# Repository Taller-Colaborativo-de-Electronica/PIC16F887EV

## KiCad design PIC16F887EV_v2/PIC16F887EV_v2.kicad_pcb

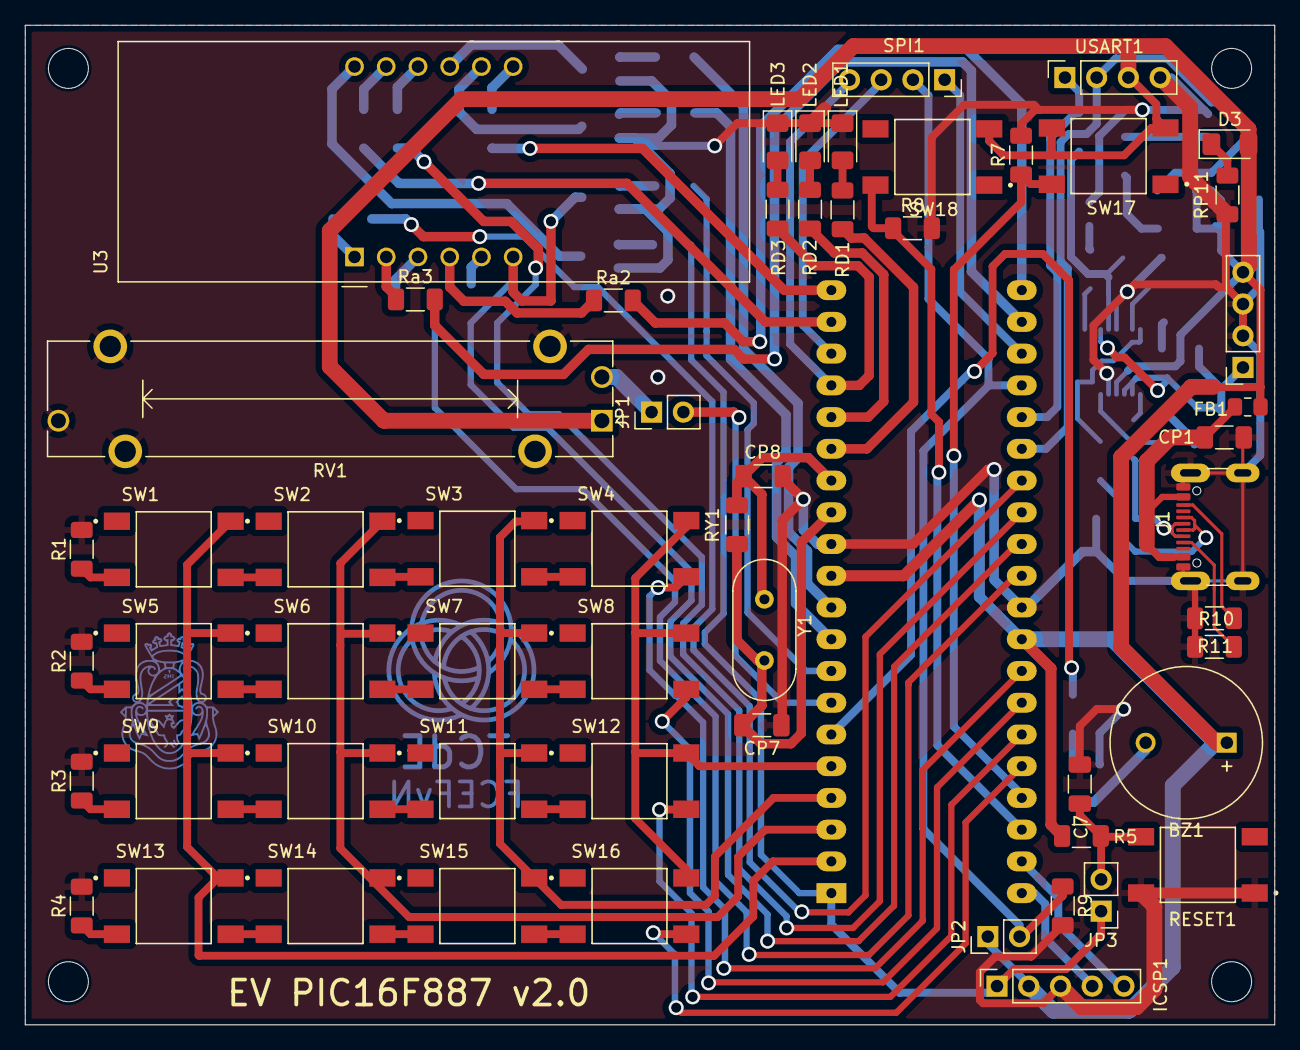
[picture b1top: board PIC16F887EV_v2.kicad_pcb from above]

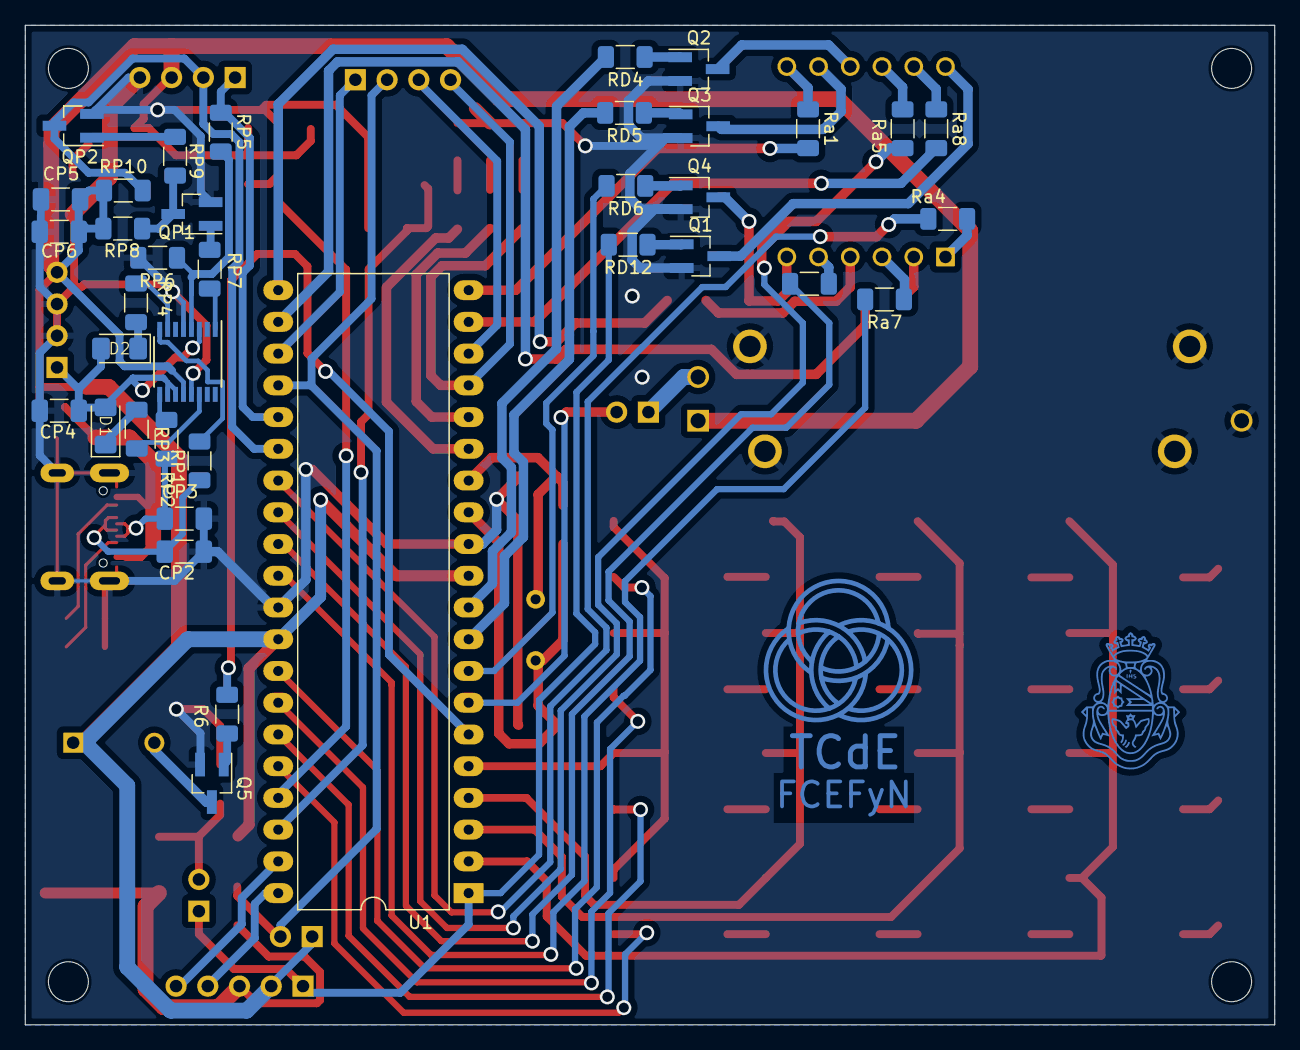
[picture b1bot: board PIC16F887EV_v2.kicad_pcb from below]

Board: 2 copper layers, 100.0 x 80.0 mm, 100 parts (39 on the bottom side), 79 nets.

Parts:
BZ1: Buzzer; MagneticBuzzer_ProSignal_ABT-410-RC
C7: 100nF; C_1206_3216Metric_Pad1.33x1.80mm_HandSolder
CP1: 10nF; C_1206_3216Metric_Pad1.33x1.80mm_HandSolder
CP2, CP3, CP7, CP8: 47pF; C_1206_3216Metric_Pad1.33x1.80mm_HandSolder
CP4, CP6: 100nF; C_1206_3216Metric_Pad1.33x1.80mm_HandSolder
CP5: 4,7uF; C_1206_3216Metric_Pad1.33x1.80mm_HandSolder
D1, D2, D3: LED; LED_1206_3216Metric_Pad1.42x1.75mm_HandSolder
FB1: FerriteBead; L_0805_2012Metric_Pad1.15x1.40mm_HandSolder
ICSP1: Conn_01x05_Socket; PinSocket_1x05_P2.54mm_Vertical
J1: USB_C_Receptacle_USB2.0_14P; USB_C_Receptacle_GCT_USB4105-xx-A_16P_TopMnt_Horizontal
JP1, JP2, JP3: Jumper_2_Bridged; PinHeader_1x02_P2.54mm_Vertical
LED1, LED2, LED3: LED; LED_1206_3216Metric_Pad1.42x1.75mm_HandSolder
POWER1: Conn_01x04; PinSocket_1x04_P2.54mm_Vertical
Q1, Q2, Q3, Q4, Q5: 2N3904; SOT-23_Handsoldering-mod
QP1, QP2: 2N3904; SOT-23_Handsoldering-mod
R1, R2, R3, R4, R5, R7, R8, R9: 10K; R_1206_3216Metric_Pad1.30x1.75mm_HandSolder
R6: 4.7k; R_1206_3216Metric_Pad1.30x1.75mm_HandSolder
R10, R11: 5.1k; R_1206_3216Metric_Pad1.30x1.75mm_HandSolder
RD1, RD2, RD3: 220R; R_1206_3216Metric_Pad1.30x1.75mm_HandSolder
RD4, RD5, RD6, RD12: 4.7k; R_1206_3216Metric_Pad1.30x1.75mm_HandSolder
REF3, REF4, REF4#2, REF4#3: MountingHole_3.2mm_M3
RESET1: SW_Push; SW_TS04-66-43-BK-100-SMT
RP1, RP2: 27R; R_1206_3216Metric_Pad1.30x1.75mm_HandSolder
RP3, RP4, RP11: 220R; R_1206_3216Metric_Pad1.30x1.75mm_HandSolder
RP5: 2K2; R_1206_3216Metric_Pad1.30x1.75mm_HandSolder
RP6: 3K3; R_1206_3216Metric_Pad1.30x1.75mm_HandSolder
RP7: 4K7; R_1206_3216Metric_Pad1.30x1.75mm_HandSolder
RP8, RP10: 10K; R_1206_3216Metric_Pad1.30x1.75mm_HandSolder
RP9: 1K; R_1206_3216Metric_Pad1.30x1.75mm_HandSolder
RV1: R_Potentiometer_MountingPin; Potentiometer_Bourns_PTA3043_Single_Slide
RY1: 10M; R_1206_3216Metric_Pad1.30x1.75mm_HandSolder
Ra1, Ra2, Ra3, Ra4, Ra5, Ra6, Ra7, Ra8: 220R; R_1206_3216Metric_Pad1.30x1.75mm_HandSolder
SPI1: Conn_01x04; PinSocket_1x04_P2.54mm_Vertical
SW1, SW2, SW3, SW4, SW5, SW6, SW7, SW8, SW9, SW10, SW11, SW12, SW13, SW14, SW15, SW16, SW17, SW18: SW_Push; SW_TS04-66-43-BK-100-SMT
TCdE FCEFYN: Logo
TCdE FCEFYN#2: Logo
U1: PIC16F887-IP; DIP-40_W15.24mm_LongPads
U2: FT230XS; SSOP-16_3.9x4.9mm_P0.635mm
U3: CC56-12EWA; CA56-12EWA
USART1: Conn_01x04; PinSocket_1x04_P2.54mm_Vertical
Y1: Crystal; Crystal_HC18-U_Vertical

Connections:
+3.3V: CP4.2, D1.2 (A), D2.2 (A), POWER1.1, U2.3 (VCCIO), U2.10 (3V3OUT), U2.11 (~RESET)
+5V: BZ1.1 (-), CP5.2, CP6.2, D3.2 (A), FB1.1, ICSP1.2, JP2.1 (A), POWER1.4, R5.1, RP8.1, RP10.1, RV1.1, SW17.2, SW18.2, U1.11 (VDD), U1.32 (VDD), U2.12 (VCC), USART1.3
DISPLAY1: Q1.3 (C), U3.12 (CC1)
DISPLAY2: Q2.3 (C), U3.9 (CC2)
DISPLAY3: Q3.3 (C), U3.8 (CC3)
DISPLAY4: Q4.3 (C), U3.6 (CC4)
DP: Ra7.1, U3.3 (DPX)
GND: C7.2, CP1.1, CP2.2, CP3.2, CP4.1, CP5.1, CP6.1, CP7.1, CP8.1, ICSP1.3, J1.A1 (GND), J1.A12 (GND), J1.B1 (GND), J1.B12 (GND), J1.S1 (SHIELD), LED1.1 (K), LED2.1 (K), LED3.1 (K), POWER1.2, POWER1.3, Q1.1 (E), Q2.1 (E), Q3.1 (E), Q4.1 (E), Q5.1 (E), QP1.1 (E), QP2.1 (E), R1.2, R2.2, R3.2, R4.2, R7.2, R8.2, R9.2, R10.2, R11.2, RESET1.1, RP6.2, RP11.2, RV1.3, RV1.MP (MountPin), U1.12 (VSS), U1.31 (VSS), U2.5 (GND), U2.13 (GND), USART1.4
ICSPCLK: ICSP1.5, U1.39 (ICSPCLK/RB6)
ICSPDAT: ICSP1.4, U1.40 (ICSPDAT/RB7)
MCLR: ICSP1.1, JP3.1 (A), RD12.2, U1.1 (RE3/~MCLR/Vpp)
unnamed: BZ1.2 (+), Q5.3 (C)
unnamed: CP1.2, FB1.2, J1.A4 (VBUS), J1.A9 (VBUS), J1.B4 (VBUS), J1.B9 (VBUS)
unnamed: CP2.1, J1.A6 (D+), J1.B6 (D+), RP1.2
unnamed: CP3.1, J1.A7 (D-), J1.B7 (D-), RP2.2
unnamed: D1.1 (K), RP3.1
unnamed: D2.1 (K), RP4.1
unnamed: D3.1 (K), RP11.1
unnamed: J1.A5 (CC1), R10.1
unnamed: J1.B5 (CC2), R11.1
unnamed: JP1.1 (A), RV1.2
unnamed: C7.1, JP3.2 (B), R5.2, RESET1.2
unnamed: LED1.2 (A), RD1.1
unnamed: LED2.2 (A), RD2.1
unnamed: LED3.2 (A), RD3.1
unnamed: Q1.2 (B), RD12.1
unnamed: Q2.2 (B), RD4.1
unnamed: Q3.2 (B), RD5.1
unnamed: Q4.2 (B), RD6.1
unnamed: Q5.2 (B), R6.1
unnamed: QP1.2 (B), RP7.1
unnamed: QP1.3 (C), RP8.2, RP9.2
unnamed: QP2.2 (B), RP9.1
unnamed: CP8.2, RY1.2, U1.14 (RA6/OSC2/CLKOUT), Y1.2
unnamed: CP7.2, RY1.1, U1.13 (RA7/OSC1/CLKIN), Y1.1
unnamed: RP3.2, U2.14 (CBUS1)
unnamed: RP4.2, U2.7 (CBUS2)
unnamed: RP5.2, RP6.1, U2.4 (RXD)
unnamed: RP7.2, U2.1 (TXD)
unnamed: RP2.1, U2.9 (USBDM)
unnamed: RP1.1, U2.8 (USBDP)
RA0: SW1.1, SW5.1, SW9.1, SW13.1, U1.2 (C12IN0-/ULPWU/AN0/RA0)
RA1: SW2.1, SW6.1, SW10.1, SW14.1, U1.3 (C12IN1-/AN1/RA1)
RA2: SW3.1, SW7.1, SW11.1, SW15.1, U1.4 (C2IN+/CVref/Vref-/AN2/RA2)
RA3: SW4.1, SW8.1, SW12.1, SW16.1, U1.5 (C1IN+/Vref+/AN3/RA3)
RA4: R6.2, U1.6 (C1OUT/T0CKI/RA4)
RA5: JP1.2 (B), U1.7 (C2OUT/~SS/AN4/RA5)
RB0: R1.1, SW1.2, SW2.2, SW3.2, SW4.2, U1.33 (INT/AN12/RB0)
RB1: R2.1, SW5.2, SW6.2, SW7.2, SW8.2, U1.34 (C12IN3-/AN10/RB1)
RB2: R3.1, SW9.2, SW10.2, SW11.2, SW12.2, U1.35 (AN8/RB2)
RB3: R4.1, SW13.2, SW14.2, SW15.2, SW16.2, U1.36 (C12IN2-/PGM/AN9/RB3)
RB4: R7.1, SW17.1, U1.37 (AN11/RB4)
RB5: R8.1, SW18.1, U1.38 (~T1G/AN13/RB5)
RC0: RD1.2, U1.15 (T10S0/T1CKI/RC0)
RC1: RD2.2, U1.16 (T1OSI/CCP2/RC1)
RC2: RD3.2, SPI1.4, U1.17 (P1A/CCP1/RC2)
RD0: Ra8.2, U1.19 (RD0)
RD1: Ra1.2, U1.20 (RD1)
RD2: Ra2.2, U1.21 (RD2)
RD3: Ra3.2, U1.22 (RD3)
RD4: Ra4.2, U1.27 (RD4)
RD5: Ra5.2, U1.28 (RD5/P1B)
RD6: Ra6.2, U1.29 (RD6/P1C)
RD7: Ra7.2, U1.30 (RD7/P1D)
RE0: RD6.2, U1.8 (RE0/AN5)
RE1: RD5.2, U1.9 (RE1/AN6)
RE2: RD4.2, U1.10 (RE2/AN7)
RXpic: QP2.3 (C), RP10.2, U1.26 (RX/DT/RC7), USART1.2
SCK: SPI1.3, U1.18 (SCL/SCK/RC3)
SDI: SPI1.1, U1.23 (SDA/SDI/RC4)
SDO: JP2.2 (B), R9.1, SPI1.2, U1.24 (SDO/RC5)
TXpic: RP5.1, U1.25 (TX/CK/RC6), USART1.1
a: Ra8.1, U3.11 (a)
b: Ra1.1, U3.7 (b)
c: Ra2.1, U3.4 (c)
d: Ra3.1, U3.2 (d)
e: Ra4.1, U3.1 (e)
f: Ra5.1, U3.10 (f)
g: Ra6.1, U3.5 (g)

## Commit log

2024-10-15 Update v1.1
    -Correccion USB C (pads, conexion shield, pines de datos, etc)
    -Correccion footprints transistores, reruteo
    -Se acomodaron los textos en silkscreen
    -Zonas sin alivios termicos
2024-10-16 Correccion v1.1
    falto una pista
2024-10-16 Cambio de nombre v2.0
2024-10-16 Revert "Cambio de nombre v2.0"
2024-10-17 Carpetas Update
    Versiones por carpeta y proyectos distintos
2024-10-17 Modif prueba branch
2024-10-18 Add prueba de commit to README.md
2024-10-31 Correccion errores v1, y finalizacion V2
2024-12-11 Ordenamiento y equidistanciamiento en RD y RB
    Cambie el ancho de pistas, las equidistancie entre si, de modo que que no queden algunas muy pegadas
2024-12-11 Ordenamiento y equidistanciamiento en RD y RB, Relleno
    Cambie el ancho de pistas, las equidistancie entre si, de modo que que no queden algunas muy pegadas.
    Relleno de zonas (el anterior lo subi sin)
